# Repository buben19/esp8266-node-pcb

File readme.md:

# ESP8266 Node PCB

Design of esp8266 board PCB. This should be base design for esp8266 IoT devices.

## Features

 - Powered by mini DC-DC power supply module ([LM2596](http://www.ti.com/lit/ds/symlink/lm2596.pdf) chip).
 - 5.5 mm center positive jack.
 - On-board programming connector.
 - Programming push button.
 - Jumper for enabling power supply module.
 - RJ-11 connector for connecting various sensors.
 - Notification LED.
 - Intended to be manufactured by [dirtypcbs.com](http://dirtypcbs.com/).
 - AVR like ISP header for in circuit programming.

## Images

## Get board

You can order PCB on this [link](http://dirtypcbs.com/store/designer/details/9988/941/esp8266-pcb-v0-1-2-zip).

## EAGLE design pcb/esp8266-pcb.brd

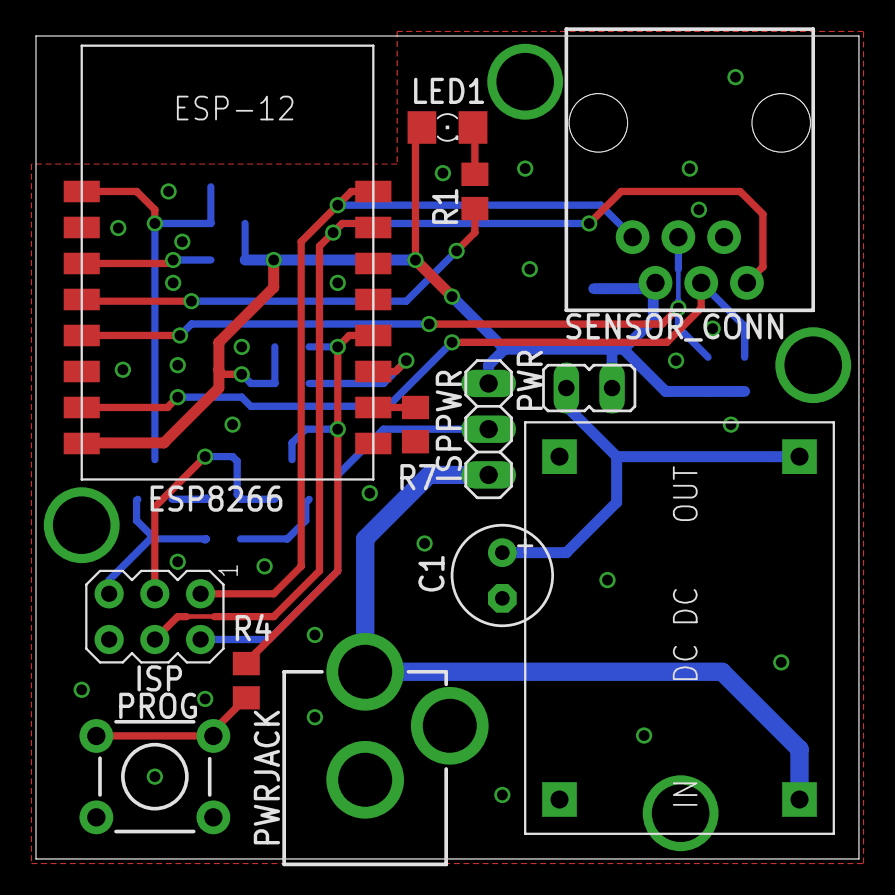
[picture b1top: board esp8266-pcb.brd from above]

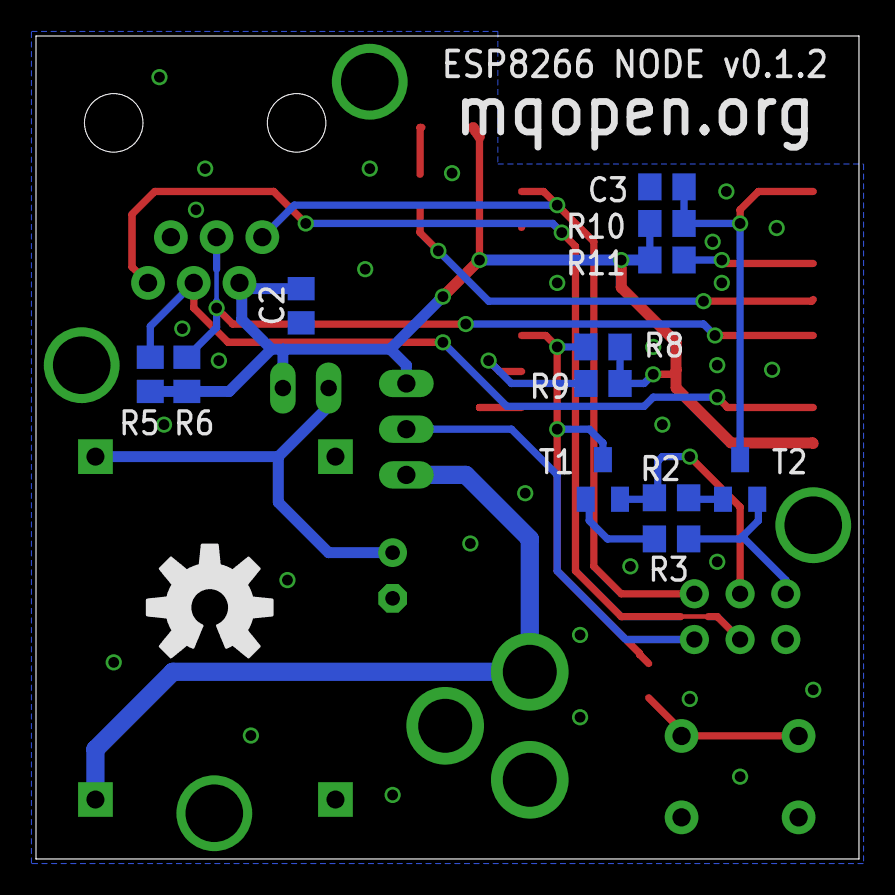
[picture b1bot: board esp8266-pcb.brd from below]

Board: 2 copper layers, 45.7 x 45.7 mm, 26 parts (13 on the bottom side), 21 nets.

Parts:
C1: 220uF; E2,5-6
C2, C3: 100nF; C0805
ESP8266: ESP8266_ESP-12; ESP8266-ESP12
ISP: AVRISP-6; AVRISP
ISPPWR: 1X03
LED1: RED; 1206
PROG: TACTILE-PTH
PWR: JP1
PWRJACK: POWER_JACKPTH; POWER_JACK_PTH
R1: 82R; R0805
R2, R3, R7, R8, R9, R10, R11: 12K; R0805
R4: 470R; R0805
R5, R6: 10K; R0805
SENSOR_CONN: RJ11; RJ11-6
T1, T2: SOT23-BEC
U$1: OSHW-LOGOL; OSHW-LOGO-L
U$2: DC-DC-SMALL; DC-DC

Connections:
+3V3: C2.2, ESP8266.16, ISPPWR.1, LED1.A, PWR.2, R5.2, R6.2, R8.2, R9.2, R10.2, R11.2, SENSOR_CONN.5
DTR: ISP.3, R2.2, T1.E
EN: ESP8266.11, R11.1
GND: C1.-, C2.1, C3.1, ESP8266.1, ISP.6, PROG.3, PROG.4, PWRJACK.GND, PWRJACK.GNDBREAK, R7.2, SENSOR_CONN.2, U$2.P$3, U$2.P$4
GPIO0: ESP8266.4, R4.1, R8.1, T1.C
GPIO2: ESP8266.3, R9.1
GPIO13: ESP8266.15, R5.1, SENSOR_CONN.3
GPIO14: ESP8266.13, R6.1, SENSOR_CONN.4
GPIO16: ESP8266.12, R1.2
unnamed: LED1.C, R1.1
unnamed: C1.+, PWR.1, U$2.P$2
unnamed: R2.1, T2.B
unnamed: PROG.1, PROG.2, R4.2
unnamed: ESP8266.2, R7.1
unnamed: ISP.2, ISPPWR.2
unnamed: R3.1, T1.B
NRST: C3.2, ESP8266.9, R10.1, T2.C
RST: ISP.5, R3.2, T2.E
RXD: ESP8266.7, ISP.4, SENSOR_CONN.1
TXD: ESP8266.8, ISP.1, SENSOR_CONN.6
VIN: ISPPWR.3, PWRJACK.PWR, U$2.P$1

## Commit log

2015-11-30 initial commit.
2016-02-01 Project refactoring.
2016-02-01 Added readme file.
2016-02-04 Removed one RJ-11 port. Added board design.
2016-02-04 Added gitignore file.
2016-02-04 Added changelog.
2016-02-04 Added mount holes.
2016-02-04 Rearanged bNames and tNames.
2016-02-04 Added vias.
2016-02-06 Added power enable jumper.
2016-02-06 Changed some routing.Changed some routing.
2016-02-07 Fixed typo at board description. Rearranged labels.
2016-02-07 Added OpenHW logo.
2016-02-08 Minor board and schematic refactoring.
2016-02-08 Updated changelog.
2016-02-08 Removed unused nets.
2016-02-09 Minor board refactoring.
2016-02-18 Changelog moved into doc directory.
2016-03-07 Added license file.
2016-03-13 GPIO15 grounded with 12K resistor.
2016-03-14 Changed board label.
2016-03-14 Notofication LED replaced with 1206 package.
2016-03-14 Component rerouting.
2016-03-24 Updated readme.
2016-03-24 Added schematic pdf and board image.
2016-03-24 Added node photos. Udpdated readme file.
2016-04-20 Updated schematics.
    Changed sensor connection pins.
    Changed pin order on ICSP header.
    Added RX and TX ping to unused RJ-11 pins.
2016-04-20 Added jumper to ICSP voltage pin.
2016-04-20 Board routing.
2016-04-20 Updated ISP header.
2016-04-20 Updated board image.
2016-04-21 Update gitignore.
2016-12-12 Added v0.1.1 images.
2016-12-12 Added new board designs.
2016-12-12 Updated gitignore.
2016-12-12 Added gerber files.

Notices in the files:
parts and their libraries:
SparkFun-Connectors: Licensing: Creative Commons ShareAlike 4.0 International - https://creativecommons.org/licenses/by-sa/4.0
SparkFun: Licensing: CC v3.0 Share-Alike You are welcome to use this library for commercial purposes.
